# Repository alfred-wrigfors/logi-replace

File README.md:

# logi-replace
Digital replacement board for Logitech speakers

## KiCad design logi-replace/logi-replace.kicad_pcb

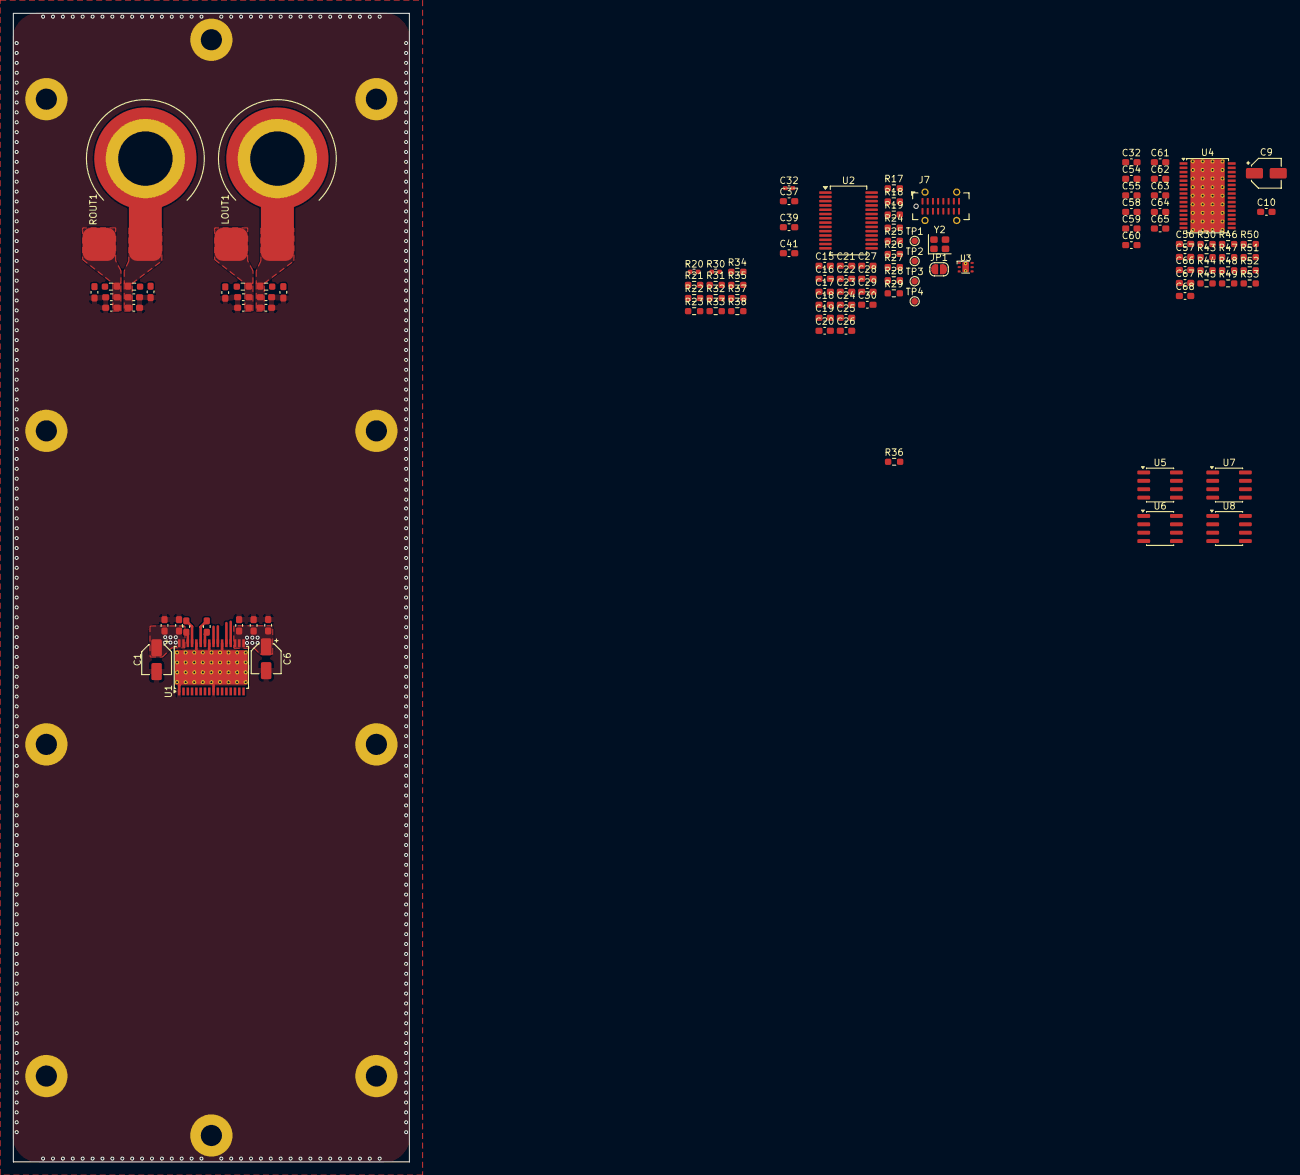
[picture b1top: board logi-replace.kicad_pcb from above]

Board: 2 copper layers, 60.0 x 174.0 mm, 124 parts (0 on the bottom side), 65 nets.

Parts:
C1, C6, C9: C; CP_Elec_4x4.5
C10, C25, C26, C31, C32#2, C33, C34, C35, C36, C37, C54, C55, C58, C61, C66: C; C_0603_1608Metric_Pad1.08x0.95mm_HandSolder
C15, C16, C17, C18, C21, C22, C23, C24, C27, C28, C29, C30, C59, C60: 1u; C_0603_1608Metric_Pad1.08x0.95mm_HandSolder
C19, C20: 10u; C_0603_1608Metric_Pad1.08x0.95mm_HandSolder
C32: 1u; C_0402_1005Metric_Pad0.74x0.62mm_HandSolder
C38, C39, C40, C41, C56, C57, C67, C68: 220u; C_0603_1608Metric_Pad1.08x0.95mm_HandSolder
C42, C43, C48, C49: 680n; C_0603_1608Metric_Pad1.08x0.95mm_HandSolder
C44, C45, C50, C51, C62, C63: 1n; C_0603_1608Metric_Pad1.08x0.95mm_HandSolder
C46, C47, C52, C53, C64, C65: 10n; C_0603_1608Metric_Pad1.08x0.95mm_HandSolder
H1, H2, H3, H4, H5, H6, H7, H8, H9, H10: MountingHole_Pad; MountingHole_3.2mm_M3_Pad
J7: USB_C_Receptacle_USB2.0_16P; USB_C_Receptacle_G-Switch_GT-USB-7051x
JP1: SolderJumper_2_Open; SolderJumper-2_P1.3mm_Open_RoundedPad1.0x1.5mm
LOUT1: RCA; REAN_Black
R17: 1k5; R_0603_1608Metric_Pad0.98x0.95mm_HandSolder
R18: 1M; R_0603_1608Metric_Pad0.98x0.95mm_HandSolder
R19: 27k; R_0603_1608Metric_Pad0.98x0.95mm_HandSolder
R20: 27k; R_0402_1005Metric_Pad0.72x0.64mm_HandSolder
R21, R30#2, R48, R50, R52: R; R_0603_1608Metric_Pad0.98x0.95mm_HandSolder
R22, R23, R24, R25, R29, R31, R32, R33, R34, R35, R47, R49, R51, R53: 5k1; R_0603_1608Metric_Pad0.98x0.95mm_HandSolder
R26, R27: 22R; R_0603_1608Metric_Pad0.98x0.95mm_HandSolder
R28: 12k; R_0603_1608Metric_Pad0.98x0.95mm_HandSolder
R30: 5k1; R_0402_1005Metric_Pad0.72x0.64mm_HandSolder
R36: 10k; R_0603_1608Metric_Pad0.98x0.95mm_HandSolder
R37: 20k; R_0603_1608Metric_Pad0.98x0.95mm_HandSolder
R38: 100k; R_0603_1608Metric_Pad0.98x0.95mm_HandSolder
R39, R40, R41, R42, R43, R44: 3R3; R_0603_1608Metric_Pad0.98x0.95mm_HandSolder
R45: 47k; R_0603_1608Metric_Pad0.98x0.95mm_HandSolder
R46: 75k; R_0603_1608Metric_Pad0.98x0.95mm_HandSolder
ROUT1: RCA; REAN_Red
TP1, TP2, TP3, TP4: TestPoint; TestPoint_Pad_D1.0mm
U1, U4: TPA311xD2-Q1; HTSSOP-32-1EP_6.1x11mm_P0.65mm_EP5.2x11mm_Mask4.11x4.36mm_T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
U2: SSOP-28_5.3x10.2mm_P0.65mm
U3: TPS7A26; WSON_6_2.00x2.00mm
U5, U6, U7, U8: NE5532; SOIC-8_3.9x4.9mm_P1.27mm
Y2: 12MHz; Crystal_SMD_2520-4Pin_2.5x2.0mm

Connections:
+24VA: C1.1, C6.1, C9.1, C10.1, C31.1, C32#2.1, C33.1, C34.1, C35.1, C36.1, C54.1, C55.1, C58.1, C61.1, R21.1, R22.1, R30#2.1, R31.1, R33.1, R48.1, R50.1, R52.1, U1.17 (AVCC), U1.18 (PVCC), U1.19 (PVCC), U1.31 (PVCC), U1.32 (PVCC), U4.17 (AVCC), U4.18 (PVCC), U4.19 (PVCC), U4.31 (PVCC), U4.32 (PVCC)
/Amp LR/AM0: R33.2, R34.1, U1.15 (AM0)
/Amp LR/AM1: R31.2, R32.1, U1.14 (AM1)
/Amp LR/AM2: R22.2, R23.1, U1.13 (AM2)
/Amp LR/BSNL: C41.2, U1.20 (BSNL)
/Amp LR/BSNR: C40.2, U1.26 (BSNR)
/Amp LR/BSPL: C39.2, U1.24 (BSPL)
/Amp LR/BSPR: C38.2, U1.30 (BSPR)
/Amp LR/GAIN/SLV: R37.1, R38.2, U1.8 (GAIN/SLV)
/Amp LR/MUTE: R35.1, U1.12 (MUTE)
/Amp LR/OUTL_N: C49.2, C51.2, LOUT1.2 (Ext), R42.2
/Amp LR/OUTL_P: C48.1, C50.1, LOUT1.1 (In), R41.1
/Amp LR/OUTNL: C41.1, U1.21 (OUTNL)
/Amp LR/OUTNR: C40.1, U1.27 (OUTNR)
/Amp LR/OUTPL: C39.1, U1.23 (OUTPL)
/Amp LR/OUTPR: C38.1, U1.29 (OUTPR)
/Amp LR/OUTR_N: C43.2, C45.2, R40.2, ROUT1.2 (Ext)
/Amp LR/OUTR_P: C42.1, C44.1, R39.1, ROUT1.1 (In)
/Amp LR/SYNC: R36.1, U1.16 (SYNC)
/Amp LR/~SD/FAULT: R21.2, U1.2 (~SD), U1.3 (~FAULT)
/Amp Sub/AM0: R52.2, R53.1, U4.15 (AM0)
/Amp Sub/AM1: R50.2, R51.1, U4.14 (AM1)
/Amp Sub/AM2: R48.2, R49.1, U4.13 (AM2)
/Amp Sub/BSN1: C56.2, U4.24 (BSPL)
/Amp Sub/BSN2: C57.2, U4.20 (BSNL)
/Amp Sub/BSP1: C67.2, U4.30 (BSPR)
/Amp Sub/BSP2: C68.2, U4.26 (BSNR)
/Amp Sub/GAIN/SLV: R45.2, R46.1, U4.8 (GAIN/SLV)
/Amp Sub/MUTE: R47.1, U4.12 (MUTE)
/Amp Sub/OUTN: C56.1, C57.1, U4.21 (OUTNL), U4.23 (OUTPL)
/Amp Sub/OUTP: C67.1, C68.1, U4.27 (OUTNR), U4.29 (OUTPR)
/Amp Sub/OUT_N: C60.2, C63.2, R44.2
/Amp Sub/OUT_P: C59.1, C62.1, R43.1
/Amp Sub/SYNC: R36.2, U4.16 (SYNC)
/Amp Sub/~SD/FAULT: R30#2.2, U4.2 (~SD), U4.3 (~FAULT)
/Audio/CC1: J7.A5 (CC1), R24.1
/Audio/CC2: J7.B5 (CC2), R25.1
/Audio/DM: R26.2, U2.2 (D-)
/Audio/DP: R27.2, U2.1 (D+)
/Audio/FB: R19.2, R28.1, U3.2 (FB)
/Audio/OUT: C30.1, JP1.1 (A), R19.1, R29.2, TP4.1 (1_1), U3.1 (OUT)
/Audio/PG: R29.1, TP3.1 (1_1), U3.3 (PG)
/Audio/VCCCI: C20.1, U2.10 (VCCCI)
/Audio/VCCP1I: C18.1, U2.17 (VCCP1I)
/Audio/VCCP2I: C17.1, U2.19 (VCCP2I)
/Audio/VCCXI: C16.1, U2.23 (VCCXI)
/Audio/VCOM: C19.1, U2.14 (VCOM)
/Audio/VINL: C23.2, U2.12 (VINL)
/Audio/VINR: C24.2, U2.13 (VINR)
/Audio/VOUTL: C27.1, U2.16 (VOUTL)
/Audio/VOUTR: C28.1, U2.15 (VOUTR)
/Audio/XTI: C25.1, R18.1, U2.21 (XTI), Y2.1
/Audio/XTO: C26.1, R18.2, U2.20 (XTO), Y2.3
/Audio/_DM: J7.A7 (D-), J7.B7 (D-), R26.1
/Audio/_DP: J7.A6 (D+), J7.B6 (D+), R17.2, R27.1
GND: C1.2, C6.2, C9.2, C10.2, C15.2, C16.2, C17.2, C18.2, C19.2, C20.2, C21.2, C22.2, C23.1, C24.1, C25.2, C26.2, C29.2, C30.2, C31.2, C32#2.2, C33.2, C34.2, C35.2, C36.2, C37.2, C42.2, C43.1, C44.2, C45.1, C46.2, C47.1, C48.2, C49.1, C50.2, C51.1, C52.2, C53.1, C54.2, C55.2, C58.2, C59.2, C60.1, C61.2, C62.2, C63.1, C64.2, C65.1, C66.2, H1.1 (1_1), H2.1 (1_1), H3.1 (1_1), H4.1 (1_1), H5.1 (1_1), H6.1 (1_1), H7.1 (1_1), H8.1 (1_1), H9.1 (1_1), H10.1 (1_1), J7.A1 (GND), J7.A12 (GND), J7.B1 (GND), J7.B12 (GND), J7.SH (SHIELD), R23.2, R24.2, R25.2, R28.2, R32.2, R34.2, R35.2, R37.2, R46.2, R47.2, R49.2, R51.2, R53.2, U1.1 (MODSEL), U1.9 (GND), U1.22 (GND), U1.25 (GND), U1.28 (GND), U1.33 (GND), U2.4 (DGNDU), U2.11 (AGNDC), U2.18 (AGNDP), U2.22 (AGNDX), U2.24 (TEST0), U2.26 (DGND), U3.5 (GND), U3.EP, U4.1 (MODSEL), U4.9 (GND), U4.10 (LINP), U4.11 (LINN), U4.22 (GND), U4.25 (GND), U4.28 (GND), U4.33 (GND), Y2.2 (G), Y2.4 (G)
GVDD_LR: C37.1, C66.1, R38.1, R45.1, U1.6 (PLIMIT), U1.7 (GVDD), U4.6 (PLIMIT), U4.7 (GVDD)
unnamed: C46.1, R39.2
unnamed: C47.2, R40.1
unnamed: C52.1, R41.2
unnamed: C53.2, R42.1
unnamed: C64.1, R43.2
unnamed: C65.2, R44.1
VBUS1: C15.1, C22.1, C29.1, J7.A4 (VBUS), J7.A9 (VBUS), J7.B4 (VBUS), J7.B9 (VBUS), TP1.1 (1_1), U2.3 (VBUS), U3.4 (EN), U3.6 (IN)
VDDI: C21.1, R17.1, TP2.1 (1_1), U2.8 (SEL0), U2.9 (SEL1), U2.27 (VDDI)
